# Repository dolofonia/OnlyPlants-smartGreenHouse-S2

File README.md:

# OnlyPlants-smartGreenHouse-S2
 HAN-Project

team:
Mark de Gast, Emiel Visser, Daan Bourgonje, Quintin Meurs, Joris Bol.

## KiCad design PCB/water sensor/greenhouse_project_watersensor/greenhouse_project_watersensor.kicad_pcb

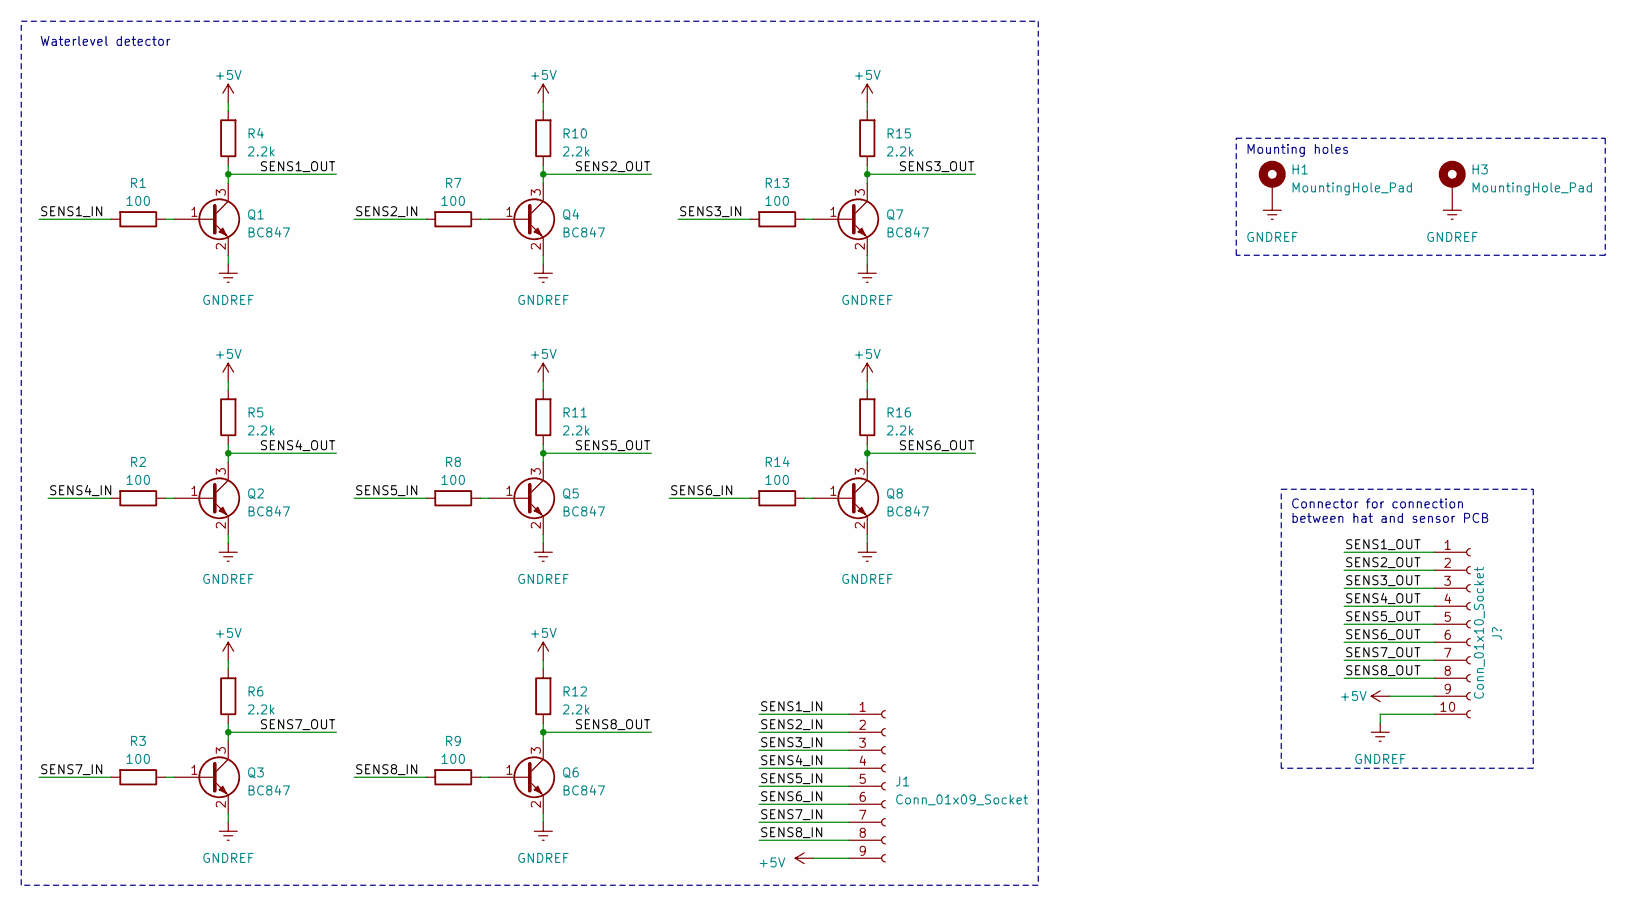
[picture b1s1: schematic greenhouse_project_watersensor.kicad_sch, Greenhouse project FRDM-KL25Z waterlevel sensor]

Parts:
H1, H3: MountingHole_Pad; MountingHole_3.2mm_M3_Pad_Via
J1: Conn_01x09_Socket; PinHeader_1x09_P2.54mm_Vertical
J3: Conn_01x10_Socket; IDC-Header_2x05_P2.54mm_Vertical
Q1, Q2, Q3, Q4, Q5, Q6, Q7, Q8: BC847; SOT-23
R1, R2, R3, R7, R8, R9, R13, R14: 100; R_1206_3216Metric_Pad1.30x1.75mm_HandSolder
R4, R5, R6, R10, R11, R12, R15, R16: 2.2k; R_1206_3216Metric_Pad1.30x1.75mm_HandSolder

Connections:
+5V: J1.9, J3.9, R4.2, R5.2, R6.2, R10.2, R11.2, R12.2, R15.2, R16.2
/SENS1_IN: J1.1, R1.2
/SENS1_OUT: J3.1, Q1.3 (C), R4.1
/SENS2_IN: J1.2, R7.2
/SENS2_OUT: J3.2, Q4.3 (C), R10.1
/SENS3_IN: J1.3, R13.2
/SENS3_OUT: J3.3, Q7.3 (C), R15.1
/SENS4_IN: J1.4, R2.2
/SENS4_OUT: J3.4, Q2.3 (C), R5.1
/SENS5_IN: J1.5, R8.2
/SENS5_OUT: J3.5, Q5.3 (C), R11.1
/SENS6_IN: J1.6, R14.2
/SENS6_OUT: J3.6, Q8.3 (C), R16.1
/SENS7_IN: J1.7, R3.2
/SENS7_OUT: J3.7, Q3.3 (C), R6.1
/SENS8_IN: J1.8, R9.2
/SENS8_OUT: J3.8, Q6.3 (C), R12.1
GNDREF: H1.1, H3.1, J3.10, Q1.2 (E), Q2.2 (E), Q3.2 (E), Q4.2 (E), Q5.2 (E), Q6.2 (E), Q7.2 (E), Q8.2 (E)
unnamed: Q1.1 (B), R1.1
unnamed: Q2.1 (B), R2.1
unnamed: Q3.1 (B), R3.1
unnamed: Q4.1 (B), R7.1
unnamed: Q5.1 (B), R8.1
unnamed: Q6.1 (B), R9.1
unnamed: Q7.1 (B), R13.1
unnamed: Q8.1 (B), R14.1

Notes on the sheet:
Mounting holes
Connector for connection between hat and sensor PCB
Waterlevel detector

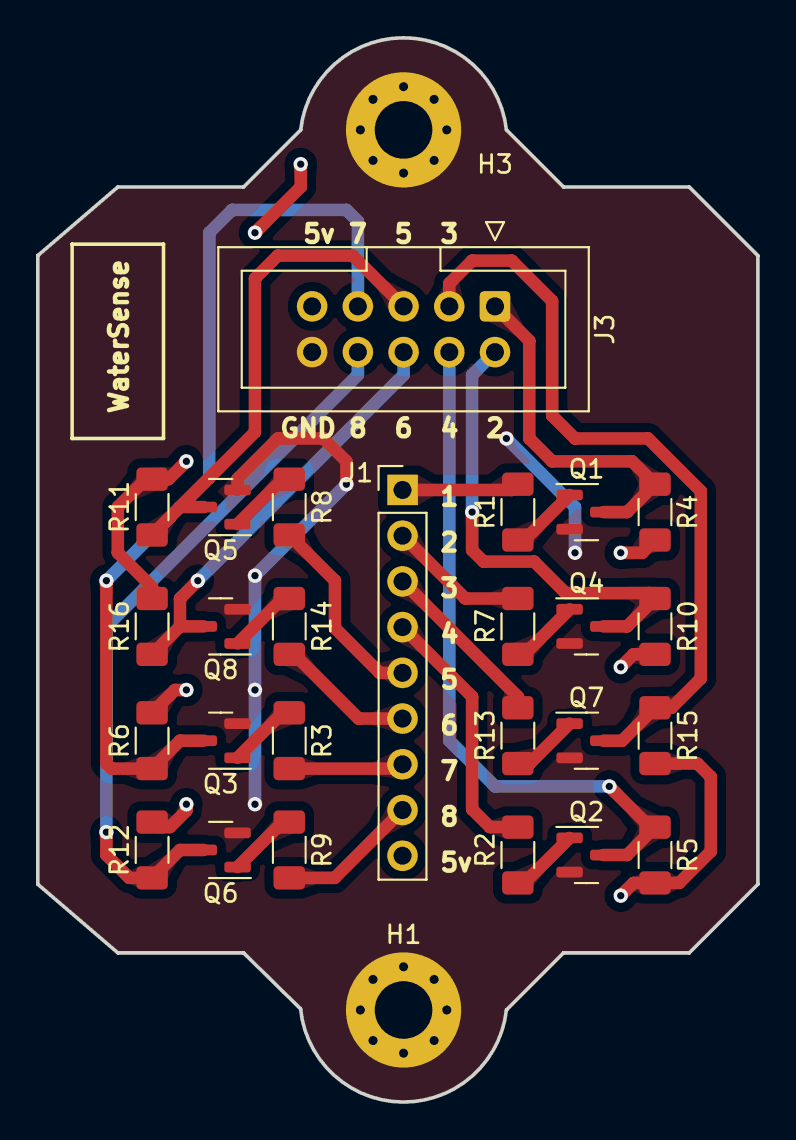
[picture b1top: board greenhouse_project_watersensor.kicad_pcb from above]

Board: 2 copper layers, 40.0 x 59.1 mm, 28 parts (0 on the bottom side), 26 nets.

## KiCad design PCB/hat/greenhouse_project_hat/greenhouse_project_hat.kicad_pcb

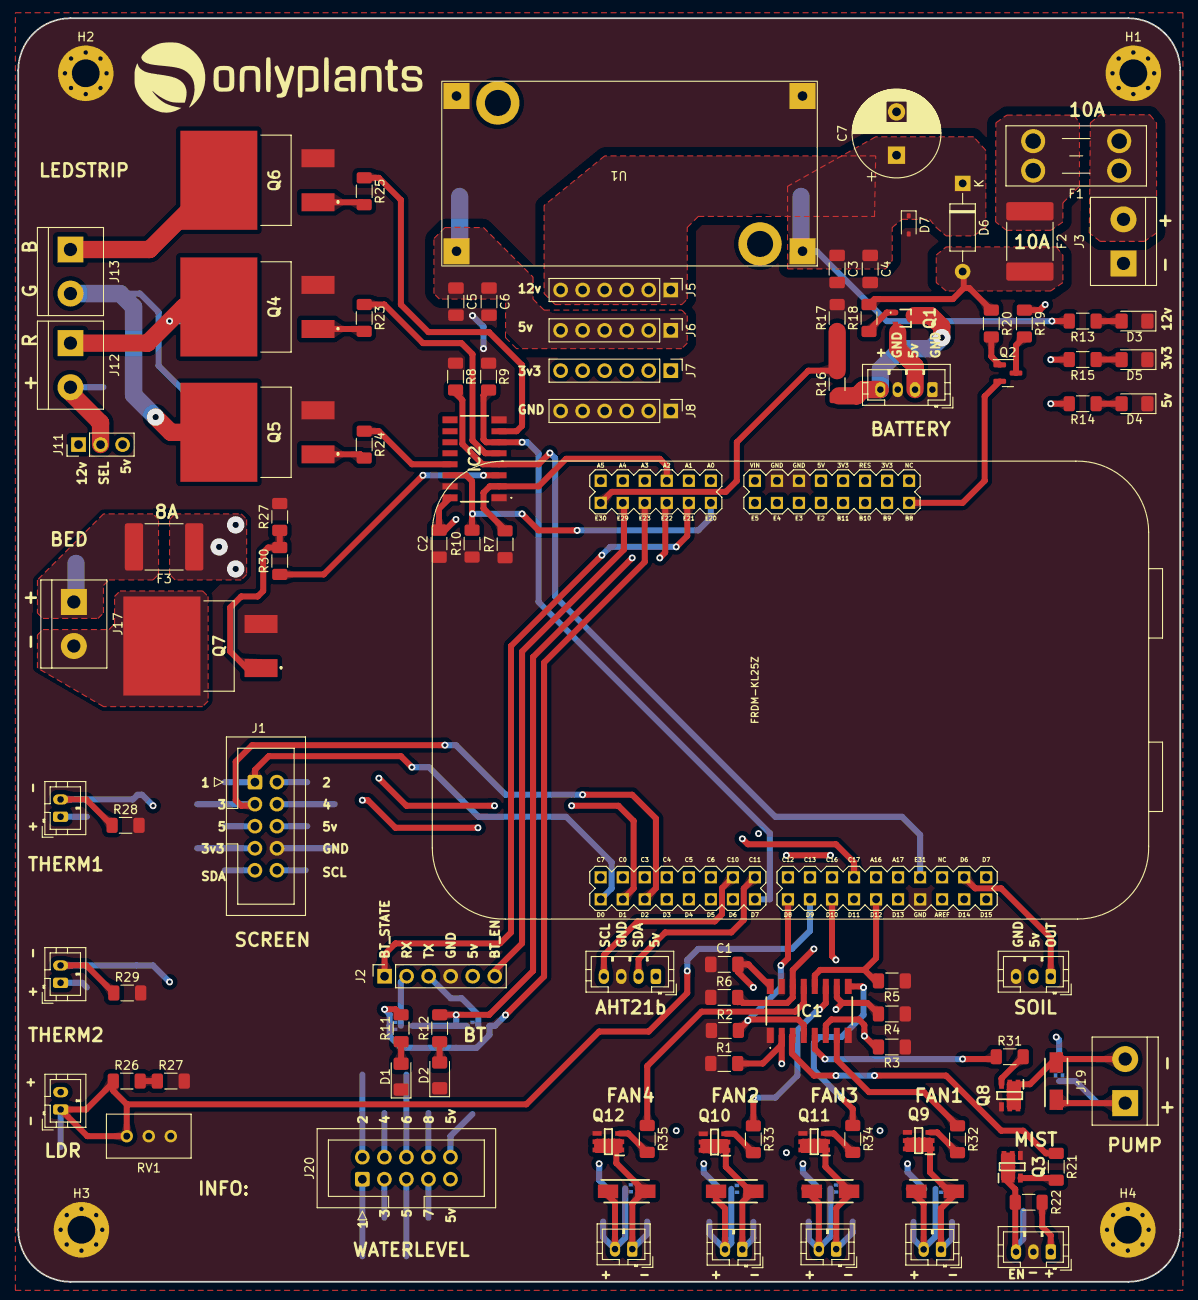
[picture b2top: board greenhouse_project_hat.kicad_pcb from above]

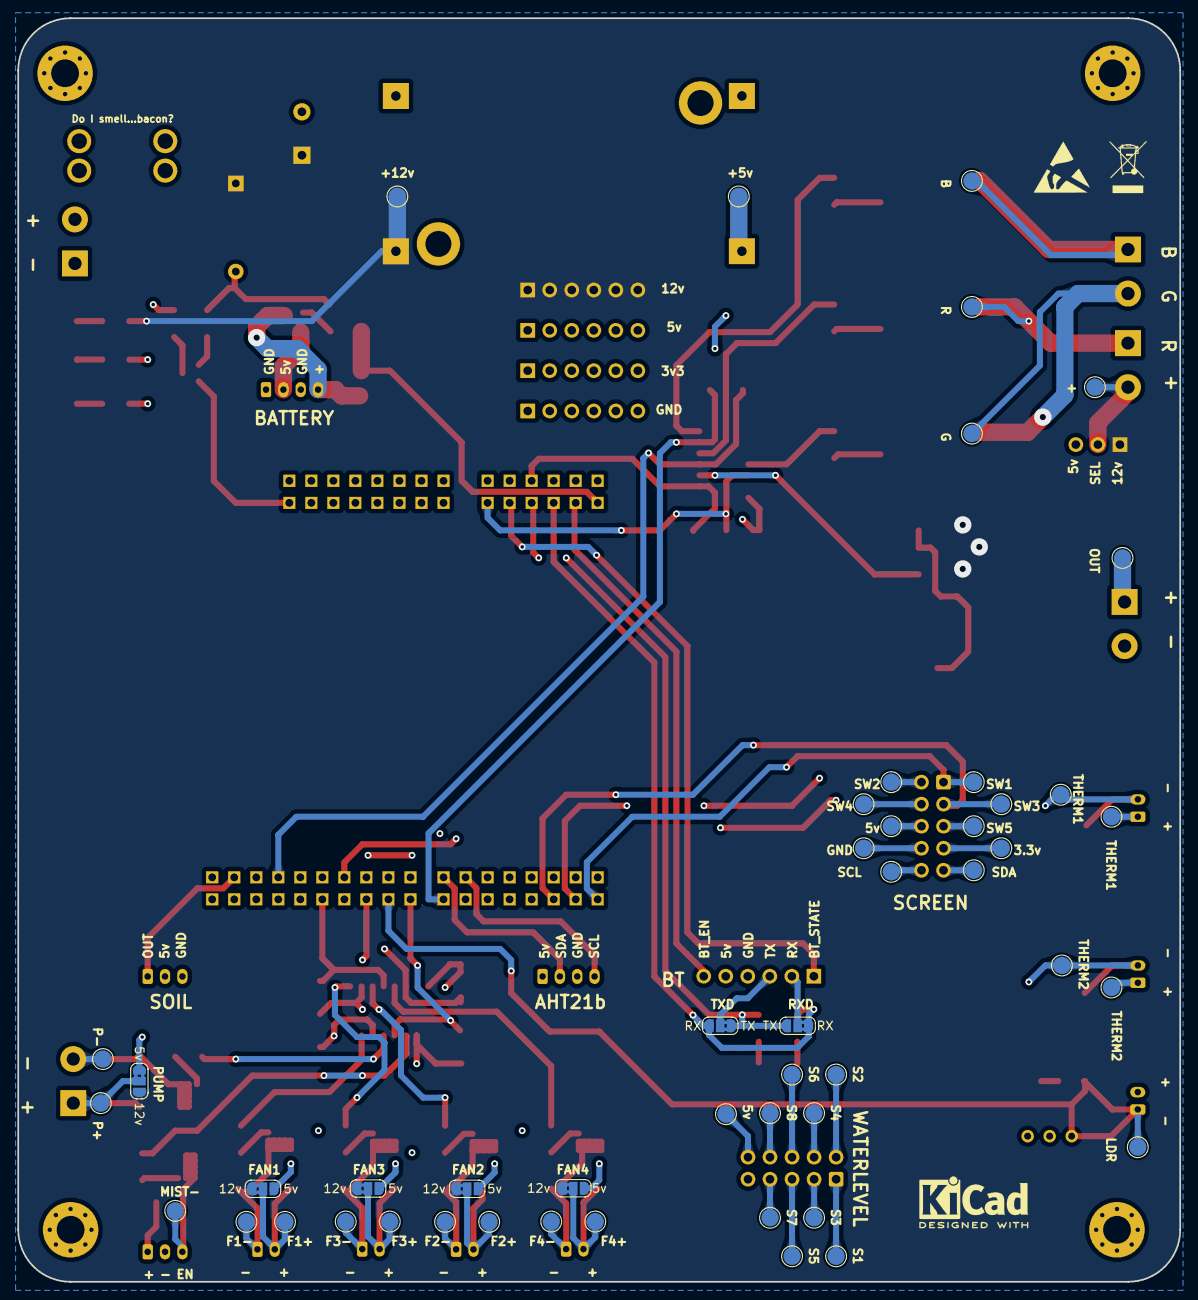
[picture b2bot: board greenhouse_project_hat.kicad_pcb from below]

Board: 4 copper layers, 134.0 x 145.7 mm, 156 parts (52 on the bottom side), 93 nets.

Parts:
C1, C2, C3, C6: 0.1uF; C_1206_3216Metric_Pad1.33x1.80mm_HandSolder
C4, C5: 10uF; C_1206_3216Metric_Pad1.33x1.80mm_HandSolder
C7: 1000uF; CP_Radial_D10.0mm_P5.00mm
D1, D2, D3, D4, D5: LED; LED_1206_3216Metric_Pad1.42x1.75mm_HandSolder
D6: D_Schottky; D_A-405_P10.16mm_Horizontal
D7: BZX384-A13-QX; D_SOD-323
D8, D9, D10, D11, D12: RS2MA-13-F; DIOM5226X230N
F1: Fuse; Fuseholder_Blade_Mini_Keystone_3568
F2, F3: Polyfuse; Fuse_2920_7451Metric_Pad2.10x5.45mm_HandSolder
FRDM1: FRDM-KL25Z; FRDM_KL25Z_NORMAL
G1: LOGO; logo
H1, H2, H3, H4: MountingHole_Pad; MountingHole_3.2mm_M3_Pad_Via
IC1, IC2: 74HCT365D,652; 74HCT365D652
J1, J20: Conn_01x10_Socket; IDC-Header_2x05_P2.54mm_Vertical
J2: Conn_01x06_Socket; PinSocket_1x06_P2.54mm_Vertical
J3, J12, J13, J17, J19: Screw_Terminal_01x02; TerminalBlock_bornier-2_P5.08mm
J4, J10: Conn_01x04_Socket; JST_PH_B4B-PH-K_1x04_P2.00mm_Vertical
J5, J6, J7, J8: Conn_01x06_Pin; PinHeader_1x06_P2.54mm_Vertical
J9, J18: Conn_01x03_Socket; JST_PH_B3B-PH-K_1x03_P2.00mm_Vertical
J11: Conn_01x03_Pin; PinHeader_1x03_P2.54mm_Vertical
J14, J15, J16, J21, J22, J23, J24: Conn_01x02_Socket; JST_PH_B2B-PH-K_1x02_P2.00mm_Vertical
JP1, JP2, JP3, JP4, JP5, JP6, JP7: Jumper_3_Bridged12; SolderJumper-3_P1.3mm_Bridged2Bar12_RoundedPad1.0x1.5mm_Num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
Q1: RZF030P01; 2SB1730
Q2: AO3401A; SOT-23
Q3, Q8, Q9, Q10, Q11, Q12: DMN6040SVT-7; SOT95P280X90-6N
Q4, Q5, Q6, Q7: IRLZ44NSTRLPBF; IRF2804STRLPBF
R1, R2, R3, R4, R5, R6, R7, R8, R9, R10, R13: 10k; R_1206_3216Metric_Pad1.30x1.75mm_HandSolder
R11, R12: 5k; R_1206_3216Metric_Pad1.30x1.75mm_HandSolder
R14, R22: 4.7k; R_1206_3216Metric_Pad1.30x1.75mm_HandSolder
R15: 2.2k; R_1206_3216Metric_Pad1.30x1.75mm_HandSolder
R16: 49.9K; R_1206_3216Metric_Pad1.30x1.75mm_HandSolder
R17: 10K; R_1206_3216Metric_Pad1.30x1.75mm_HandSolder
R18, R19, R20: 165; R_1206_3216Metric_Pad1.30x1.75mm_HandSolder
R21, R23, R24, R25, R30, R31, R32, R33, R34, R35: 1k; R_1206_3216Metric_Pad1.30x1.75mm_HandSolder
R26, R28, R29: 100k; R_1206_3216Metric_Pad1.30x1.75mm_HandSolder
R27: 12k; R_1206_3216Metric_Pad1.30x1.75mm_HandSolder
R27#2: 0; R_1206_3216Metric_Pad1.30x1.75mm_HandSolder
REF1: KiCad-Logo2_5mm_SilkScreen
REF2: WEEE-Logo_4.2x6mm_SilkScreen
REF3: ESD-Logo_6.6x6mm_SilkScreen
RV1: R_Potentiometer; Potentiometer_Bourns_3296W_Vertical
TP1, TP2, TP3, TP4, TP5, TP6, TP7, TP8, TP9, TP10, TP11, TP12, TP13, TP14, TP15, TP16, TP17, TP18, TP19, TP20, TP21, TP22, TP23, TP24, TP25, TP26, TP27, TP28, TP29, TP30, TP31, TP32, TP33, TP34, TP35, TP36, TP37, TP38, TP39, TP40, TP41, TP42: TestPoint; TestPoint_Pad_D2.0mm
U1: LM2596 Buck; LM2596_Buck_module

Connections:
+3.3V: FRDM1.P3V3 (3V3), J1.7, J7.1, J7.2, J7.3, J7.4, J7.5, J7.6, J14.2, J15.1, J16.1, R15.2, R19.1, TP7.1, TP19.1, TP20.1
+5V: C1.2, C2.2, C5.1, C6.1, FRDM1.VIN, IC1.16 (VCC), IC2.16 (VCC), J1.6, J2.5, J4.2, J6.1, J6.2, J6.3, J6.4, J6.5, J6.6, J9.1, J10.1, J11.3, J18.2, J20.9, J20.10, JP3.1 (A), JP4.3 (B), JP5.3 (B), JP6.3 (B), JP7.3 (B), Q1.2, R14.2, R22.2, TP6.1, TP11.1, TP34.1, U1.3 (OUT+)
+12V: C3.1, C4.1, C7.1, D6.1 (K), D7.1 (K), F3.1, J5.1, J5.2, J5.3, J5.4, J5.5, J5.6, J11.1, JP3.3 (B), JP4.1 (A), JP5.1 (A), JP6.1 (A), JP7.1 (A), R13.2, TP12.1, U1.1 (IN+)
/BT_EN: FRDM1.PTE29, J2.6
/BT_RXD: FRDM1.PTE23, JP1.1 (A), JP2.3 (B), R11.2
/BT_RXD_O: J2.2, JP1.2 (C)
/BT_STATE: FRDM1.PTE21, J2.1
/BT_TXD: FRDM1.PTE22, JP1.3 (B), JP2.1 (A), R12.2
/BT_TXD_O: J2.3, JP2.2 (C)
/Fans/Fan1+: D9.1, J21.2, JP4.2 (C), TP37.1
/Fans/Fan1-: D9.2, J21.1, Q9.1 (D_1), Q9.2 (D_2), Q9.5 (D_3), Q9.6 (D_4), TP35.1
/Fans/Fan2+: D10.1, J22.2, JP5.2 (C), TP38.1
/Fans/Fan2-: D10.2, J22.1, Q10.1 (D_1), Q10.2 (D_2), Q10.5 (D_3), Q10.6 (D_4), TP36.1
/Fans/Fan3+: D11.1, J23.2, JP6.2 (C), TP41.1
/Fans/Fan3-: D11.2, J23.1, Q11.1 (D_1), Q11.2 (D_2), Q11.5 (D_3), Q11.6 (D_4), TP39.1
/Fans/Fan4+: D12.1, J24.2, JP7.2 (C), TP42.1
/Fans/Fan4-: D12.2, J24.1, Q12.1 (D_1), Q12.2 (D_2), Q12.5 (D_3), Q12.6 (D_4), TP40.1
/Heating/BED_OUT: F3.2, J17.1, TP23.1
/Humidifier/MIST-: J9.3, Q3.1 (D_1), Q3.2 (D_2), Q3.5 (D_3), Q3.6 (D_4), R22.1, TP13.1
/OLED_SCL: FRDM1.D15 (SCL/PTE1), J1.10, TP10.1
/OLED_SDA: FRDM1.D14 (SDA/PTE0), J1.9, TP9.1
/Power/BATT_EN: D6.2 (A), F2.2, R18.2, R20.1
/Power/BATT_IN: J4.4, Q1.3, R16.1
/SW1_OUT: FRDM1.D0 (D0/PTA1), J1.1, TP1.1
/SW2_OUT: FRDM1.D1 (D1/PTA2), J1.2, TP2.1
/SW3_OUT: FRDM1.D2 (D2/PTD4), J1.3, TP3.1
/SW4_OUT: FRDM1.D3 (D3/PTA12), J1.4, TP4.1
/SW5_OUT: FRDM1.D4 (D4/PTA4), J1.5, TP5.1
/Water/Pump+: D8.1, J19.1, JP3.2 (C), TP25.1
/Water/Pump-: D8.2, J19.2, Q8.1 (D_1), Q8.2 (D_2), Q8.5 (D_3), Q8.6 (D_4), TP24.1
AHT_SCL: FRDM1.PTC10, J10.4
AHT_SDA: FRDM1.PTC11, J10.2
BATT_V: FRDM1.PTE30, R16.2, R17.1
B_IN: FRDM1.D7 (D7/PTC9), IC2.6 (3A), R9.2
B_IN_POW: IC2.7 (3Y), R25.1
FAN1_IN: FRDM1.D10 (D10/PTD0), IC1.6 (3A), R3.2
FAN1_IN_POW: IC1.7 (3Y), R32.1
FAN2_IN: FRDM1.D11 (D11/PTD2), IC1.10 (4A), R4.2
FAN2_IN_POW: IC1.9 (4Y), R34.1
FAN3_IN: FRDM1.D12 (D12/PTD3), IC1.12 (5A), R5.2
FAN3_IN_POW: IC1.11 (5Y), R33.1
FAN4_IN: FRDM1.D13 (D13/PTD1), IC1.14 (6A), R6.2
FAN4_IN_POW: IC1.13 (6Y), R35.1
GNDREF: C1.1, C2.1, C3.2, C4.2, C5.2, C6.2, C7.2, D1.1 (K), D2.1 (K), D3.1 (K), D4.1 (K), D5.1 (K), D7.2 (A), FRDM1.GND0, FRDM1.GND1, FRDM1.GND2, H1.1, H2.1, H3.1, H4.1, IC1.1 (~OE1), IC1.8 (GND), IC1.15 (~OE2), IC2.1 (~OE1), IC2.8 (GND), IC2.15 (~OE2), J1.8, J2.4, J3.1, J4.1, J4.3, J8.1, J8.2, J8.3, J8.4, J8.5, J8.6, J9.2, J10.3, J18.3, Q3.4 (S), Q4.3, Q5.3, Q6.3, Q7.3, Q8.4 (S), Q9.4 (S), Q10.4 (S), Q11.4 (S), Q12.4 (S), R1.1, R2.1, R3.1, R4.1, R5.1, R6.1, R7.1, R8.1, R9.1, R10.1, R17.2, R27.2, R27#2.2, R28.2, R29.2, RV1.2, RV1.3, TP8.1, U1.2 (IN-), U1.4 (OUT-)
G_IN: FRDM1.PTE20, IC2.14 (6A), R10.2
G_IN_POW: IC2.13 (6Y), R24.1
HEATER_IN: FRDM1.A2 (A2/PTB2), IC2.2 (1A), R7.2
HEATER_IN_POW: IC2.3 (1Y), R30.1
HUM_OUT: FRDM1.PTD6, J18.1
LDR_OUT: FRDM1.D9 (D9/PTD5), J14.1, R26.1, RV1.1, TP18.1
MIST_EN: FRDM1.PTC6, IC1.2 (1A), R1.2
MIST_EN_POW: IC1.3 (1Y), R21.1
unnamed: D1.2 (A), R11.1
unnamed: D2.2 (A), R12.1
unnamed: D3.2 (A), R13.1
unnamed: D4.2 (A), R14.1
unnamed: D5.2 (A), R15.1
unnamed: F1.2, F2.1
unnamed: J11.2, J12.2, TP17.1
unnamed: J12.1, Q4.2, TP14.1
unnamed: J13.1, Q6.2, TP16.1
unnamed: J13.2, Q5.2, TP15.1
unnamed: J17.2, Q7.2
unnamed: Q1.1, R18.1
unnamed: Q2.3 (D), R19.2
unnamed: Q2.1 (G), R20.2
unnamed: Q3.3 (G), R21.2
unnamed: Q4.1, R23.2
unnamed: Q5.1, R24.2
unnamed: Q6.1, R25.2
unnamed: Q7.1, R27.1, R30.2
unnamed: Q8.3 (G), R31.2
unnamed: Q9.3 (G), R32.2
unnamed: Q10.3 (G), R33.2
unnamed: Q11.3 (G), R34.2
unnamed: Q12.3 (G), R35.2
unnamed: R26.2, R27#2.1
PUMP_IN: FRDM1.D8 (D8/PTA13), IC1.4 (2A), R2.2
PUMP_IN_POW: IC1.5 (2Y), R31.1
R_IN: FRDM1.PTE31, IC2.4 (2A), R8.2
R_IN_POW: IC2.5 (2Y), R23.1
SENS1: FRDM1.PTC12, J20.1, TP26.1
SENS2: FRDM1.PTC13, J20.2, TP27.1
SENS3: FRDM1.PTC16, J20.3, TP28.1
SENS4: FRDM1.PTC17, J20.4, TP29.1
SENS5: FRDM1.PTA16, J20.5, TP30.1
SENS6: FRDM1.PTA17, J20.6, TP31.1
SENS7: FRDM1.D5 (D5/PTA5), J20.7, TP32.1
SENS8: FRDM1.PTD7, J20.8, TP33.1
THERM1: FRDM1.A0 (A0/PTB0), J15.2, R28.1, TP22.1
THERM2: FRDM1.A1 (A1/PTB1), J16.2, R29.1, TP21.1
VDC: F1.1, J3.2
~12V_EN: FRDM1.PTB8, Q2.2 (S)

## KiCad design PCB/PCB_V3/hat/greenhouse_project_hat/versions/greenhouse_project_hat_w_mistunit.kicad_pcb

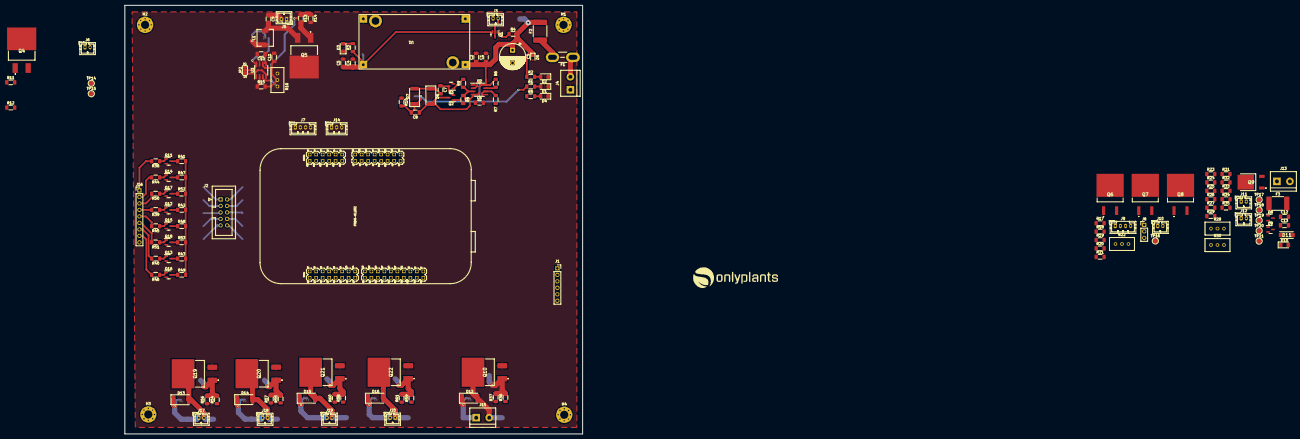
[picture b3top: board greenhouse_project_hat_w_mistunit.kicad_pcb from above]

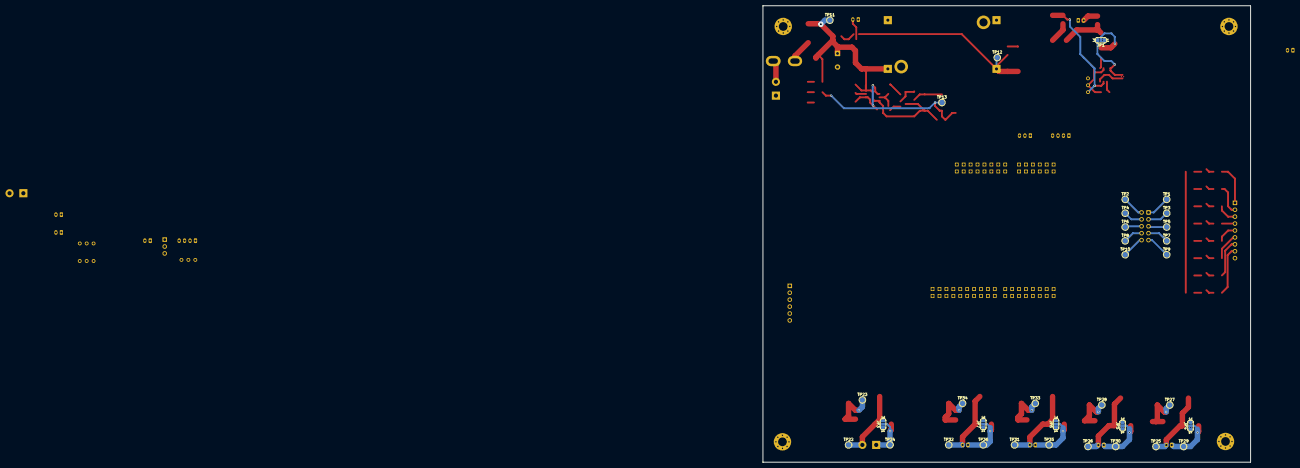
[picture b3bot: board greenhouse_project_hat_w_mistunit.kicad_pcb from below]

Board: 2 copper layers, 179.1 x 167.6 mm, 187 parts (34 on the bottom side), 90 nets.

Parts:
C1, C5, C12, C13: 0.1uF; C_1206_3216Metric_Pad1.33x1.80mm_HandSolder
C2, C4: 10uF; C_1206_3216Metric_Pad1.33x1.80mm_HandSolder
C3: 1000uF; CP_Radial_D10.0mm_P5.00mm
C6: 470nF; C_1206_3216Metric_Pad1.33x1.80mm_HandSolder
C7: 330uF; C_1206_3216Metric_Pad1.33x1.80mm_HandSolder
C8: 3.3nF; C_1206_3216Metric_Pad1.33x1.80mm_HandSolder
C9, C10: 100nF; C_1206_3216Metric_Pad1.33x1.80mm_HandSolder
C11: 10nF; C_1206_3216Metric_Pad1.33x1.80mm_HandSolder
D1, D2, D3, D4, D10: LED; LED_1206_3216Metric_Pad1.42x1.75mm_HandSolder
D5: BZX384-A13-QX; D_SOD-323
D6, D7, D12, D13, D14, D15, D16: 1N4007; D_2512_6332Metric_Pad1.52x3.35mm_HandSolder
D8, D9: BAV99; SOT-23
D11: SS54; DIOM5126X245N
F1: Fuse; Fuse_Blade_Mini_directSolder
F2, F3: Polyfuse; Fuse_2920_7451Metric_Pad2.10x5.45mm_HandSolder
FRDM1: FRDM-KL25Z; FRDM_KL25Z_NORMAL
H1, H2, H3, H4: MountingHole_Pad; MountingHole_3.2mm_M3_Pad_Via
J1: Conn_01x06_Socket; PinSocket_1x06_P2.54mm_Vertical
J2: Conn_01x10_Socket; IDC-Header_2x05_P2.54mm_Vertical
J3, J5, J6, J10, J11, J12, J17, J18, J19, J20: Conn_01x02_Socket; JST_PH_B2B-PH-K_1x02_P2.00mm_Vertical
J4, J13, J15: Screw_Terminal_01x02; TerminalBlock_bornier-2_P5.08mm
J7, J9: Conn_01x04_Socket; JST_PH_B4B-PH-K_1x04_P2.00mm_Vertical
J8: Conn_01x03_Pin; PinHeader_1x03_P2.54mm_Vertical
J14: Conn_01x03_Socket; JST_PH_B3B-PH-K_1x03_P2.00mm_Vertical
J16: Conn_01x09_Socket; PinHeader_1x09_P2.54mm_Vertical
JP1, JP2, JP3, JP4, JP5, JP6, JP7: Jumper_3_Bridged12; SolderJumper-3_P1.3mm_Bridged2Bar12_RoundedPad1.0x1.5mm_Num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
L1: 220uH; L_6.3x6.3_H3
Q1: AO3401A; SOT-23
Q2, Q3, Q11, Q12, Q13, Q14, Q15, Q16, Q17, Q18: BC847; SOT-23
Q4, Q5, Q10, Q19, Q20, Q21, Q22: IRLZ44NSTRLPBF; IRF2804STRLPBF
Q6, Q7, Q8: IRF640S
Q9: IPD036N04LGATMA1
R1: 750; R_1206_3216Metric_Pad1.30x1.75mm_HandSolder
R2, R12, R17, R18, R19, R33, R37, R56, R57, R60, R61: 10k; R_1206_3216Metric_Pad1.30x1.75mm_HandSolder
R3, R23, R24, R35: 4.7k; R_1206_3216Metric_Pad1.30x1.75mm_HandSolder
R4: 165; R_1206_3216Metric_Pad1.30x1.75mm_HandSolder
R5, R11, R36, R41, R42, R43, R47, R48, R49, R52, R53, R54, R55, R58, R59: 2.2k; R_1206_3216Metric_Pad1.30x1.75mm_HandSolder
R6: 1k; R_1206_3216Metric_Pad1.30x1.75mm_HandSolder
R7: 3.3k; R_1206_3216Metric_Pad1.30x1.75mm_HandSolder
R8, R9: 820; R_1206_3216Metric_Pad1.30x1.75mm_HandSolder
R10: 25; R_1206_3216Metric_Pad1.30x1.75mm_HandSolder
R13, R15: 10; R_1206_3216Metric_Pad1.30x1.75mm_HandSolder
R14, R21, R31, R32: 0; R_1206_3216Metric_Pad1.30x1.75mm_HandSolder
R16, R22, R28, R30: R_Variable; Potentiometer_Bourns_3296W_Vertical
R20: 100k; R_1206_3216Metric_Pad1.30x1.75mm_HandSolder
R25, R26, R27, R29: 2.37k 1%; R_1206_3216Metric_Pad1.30x1.75mm_HandSolder
R34: 12k; R_1206_3216Metric_Pad1.30x1.75mm_HandSolder
R38, R39, R40, R44, R45, R46, R50, R51: 100; R_1206_3216Metric_Pad1.30x1.75mm_HandSolder
TP1, TP2, TP3, TP4, TP5, TP6, TP7, TP8, TP9, TP10, TP11, TP12, TP13, TP14, TP15, TP16, TP17, TP18, TP19, TP20, TP21, TP22, TP23, TP24, TP25, TP26, TP27, TP28, TP29, TP30, TP31, TP32, TP33, TP34, TP35, TP36: TestPoint; TestPoint_Pad_D2.0mm
U1: LM2596 Buck; LM2596_Buck_module
U2, U3: NE555D; SOIC-8_3.9x4.9mm_P1.27mm

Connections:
+3.3V: D8.1 (K), D9.1 (K), J2.7, R5.1, R23.1, R24.1, TP7.1
+12V: C1.1, C2.1, C3.1, C8.1, D5.1 (K), D6.2 (A), F2.2, F3.1, J8.1, JP1.1 (A), JP3.3 (B), JP4.1 (A), JP5.1 (A), JP6.1 (A), JP7.1 (A), Q2.3 (C), R2.1, R4.2, R6.1, TP11.1, U1.1 (IN+), U2.4 (R), U2.8 (VCC)
+15V: C8.2, D7.1 (K), JP1.3 (B), JP2.2 (C), R1.1, R10.2, TP13.1, U3.8 (VCC)
/Fans/Fan1+: D13.1 (K), J17.1, JP4.2 (C), TP29.1
/Fans/Fan1-: D13.2 (A), J17.2, Q19.2, TP25.1
/Fans/Fan2+: D14.1 (K), J18.1, JP5.2 (C), TP30.1
/Fans/Fan2-: D14.2 (A), J18.2, Q20.2, TP26.1
/Fans/Fan3+: D15.1 (K), J19.1, JP6.2 (C), TP35.1
/Fans/Fan3-: D15.2 (A), J19.2, Q21.2, TP31.1
/Fans/Fan4+: D16.1 (K), J20.1, JP7.2 (C), TP36.1
/Fans/Fan4-: D16.2 (A), J20.2, Q22.2, TP32.1
/Heating/BED_OUT: D10.1 (K), D11.2, J13.1, Q9.2, TP21.1
/Humidifier/MIST-: J6.2, Q4.2, TP15.1
/Humidifier/piezo+: C9.1, J5.2
/OLED_SCL: J2.10, TP10.1
/OLED_SDA: J2.9, TP9.1
/OUT_SW1: J2.1, TP1.1
/OUT_SW2: J2.2, TP2.1
/OUT_SW3: J2.3, TP3.1
/OUT_SW4: J2.4, TP4.1
/OUT_SW5: J2.5, TP5.1
/Power/BATT_IN: J3.2, Q1.3 (D)
/Water/Pump+: D12.1 (K), J15.1, JP3.2 (C), TP24.1
/Water/Pump-: D12.2 (A), J15.2, Q10.2, TP22.1
ANODE: C4.1, C5.1, J1.5, J2.6, J6.1, J7.1, J8.3, J10.2, J14.2, J16.9, JP3.1 (A), JP4.3 (B), JP5.3 (B), JP6.3 (B), JP7.3 (B), Q1.2 (S), R3.1, R41.2, R42.2, R43.2, R47.2, R48.2, R49.2, R52.2, R53.2, TP6.1, TP12.1, U1.3 (OUT+)
B_IN: Q8.1, R19.1
GNDREF: C1.2, C2.2, C3.2, C4.2, C5.2, C6.2, C10.2, C11.2, C12.2, C13.2, D1.1 (K), D2.1 (K), D3.1 (K), D4.1 (K), D5.2 (A), D8.2 (A), D9.2 (A), H1.1, H2.1, H3.1, H4.1, J1.4, J2.8, J3.1, J4.1, J5.1, J7.3, J11.2, J12.2, J13.2, J14.3, Q3.2 (E), Q4.3, Q5.2, Q6.3, Q7.3, Q8.3, Q9.3, Q10.3, Q11.2 (E), Q12.2 (E), Q13.2 (E), Q14.2 (E), Q15.2 (E), Q16.2 (E), Q17.2 (E), Q18.2 (E), Q19.3, Q20.3, Q21.3, Q22.3, R10.1, R12.1, R17.2, R18.2, R19.2, R21.1, R22.2, R34.2, R37.1, R56.1, R57.1, R60.1, R61.1, TP8.1, U1.2 (IN-), U1.4 (OUT-), U1.5 (GND1), U1.6 (GND2), U2.1 (GND), U3.1 (GND)
G_IN: Q7.1, R18.1
LDR_OUT: J10.1, R20.1, R22.1, TP16.1
MIST_EN: R11.1, R15.1, U3.2 (TR)
unnamed: C9.2, L1.2, Q5.3
unnamed: D1.2 (A), R1.2
unnamed: D2.2 (A), R2.2
unnamed: D3.2 (A), R3.2
unnamed: D4.2 (A), R5.2
unnamed: C7.2, D6.1 (K), D7.2 (A)
unnamed: D8.3 (K), R25.2, R27.1, R28.1
unnamed: D9.3 (K), R26.2, R29.1, R30.1
unnamed: D10.2 (A), R35.1
unnamed: D11.1, F3.2, R35.2
unnamed: F1.2, F2.1
unnamed: J8.2, J9.1
unnamed: J9.2, Q6.2
unnamed: J9.3, Q7.2
unnamed: J9.4, Q8.2
unnamed: J11.1, R23.2, R25.1, TP17.1
unnamed: J12.1, R24.2, R26.1, TP18.1
unnamed: JP1.2 (C), L1.1
unnamed: JP2.1 (A), U3.4 (R)
unnamed: Q1.1 (G), R4.1
unnamed: Q2.1 (B), R8.2
unnamed: C7.1, Q2.2 (E), Q3.3 (C)
unnamed: Q3.1 (B), R9.2
unnamed: Q4.1, R11.2, R12.2, TP14.1
unnamed: Q5.1, R13.2
unnamed: Q9.1, R33.1, R34.1
unnamed: Q10.1, R36.2, R37.2, TP23.1
unnamed: Q11.1 (B), R38.1
unnamed: Q12.1 (B), R39.1
unnamed: Q13.1 (B), R40.1
unnamed: Q14.1 (B), R44.1
unnamed: Q15.1 (B), R45.1
unnamed: Q16.1 (B), R46.1
unnamed: Q17.1 (B), R50.1
unnamed: Q18.1 (B), R51.1
unnamed: Q19.1, R54.2, R56.2, TP27.1
unnamed: Q20.1, R55.2, R57.2, TP28.1
unnamed: Q21.1, R58.2, R60.2, TP33.1
unnamed: Q22.1, R59.2, R61.2, TP34.1
unnamed: R20.2, R21.2
unnamed: R27.2, R31.1
unnamed: R29.2, R32.1
unnamed: R6.2, R7.1, U2.7 (DIS)
unnamed: R8.1, R9.1, U2.3 (Q)
unnamed: C6.1, R7.2, U2.2 (TR), U2.6 (THR)
unnamed: C10.1, U3.5 (CV)
unnamed: C11.1, R15.2, R16.2, U3.6 (THR)
R_IN: Q6.1, R17.1
SENS1: J16.1, Q11.3 (C), R38.2, R41.1
SENS2: J16.2, Q14.3 (C), R44.2, R47.1
SENS3: J16.3, Q17.3 (C), R50.2, R52.1
SENS4: J16.4, Q12.3 (C), R39.2, R42.1
SENS5: J16.5, Q15.3 (C), R45.2, R48.1
SENS6: J16.6, Q18.3 (C), R51.2, R53.1
SENS7: J16.7, Q13.3 (C), R40.2, R43.1
SENS8: J16.8, Q16.3 (C), R46.2, R49.1
THERM0: C12.1, R28.2, R31.2, TP19.1
THERM1: C13.1, R30.2, R32.2, TP20.1
VDC: F1.1, J4.2
adj: R13.1, R14.1, R16.1, U3.3 (Q)

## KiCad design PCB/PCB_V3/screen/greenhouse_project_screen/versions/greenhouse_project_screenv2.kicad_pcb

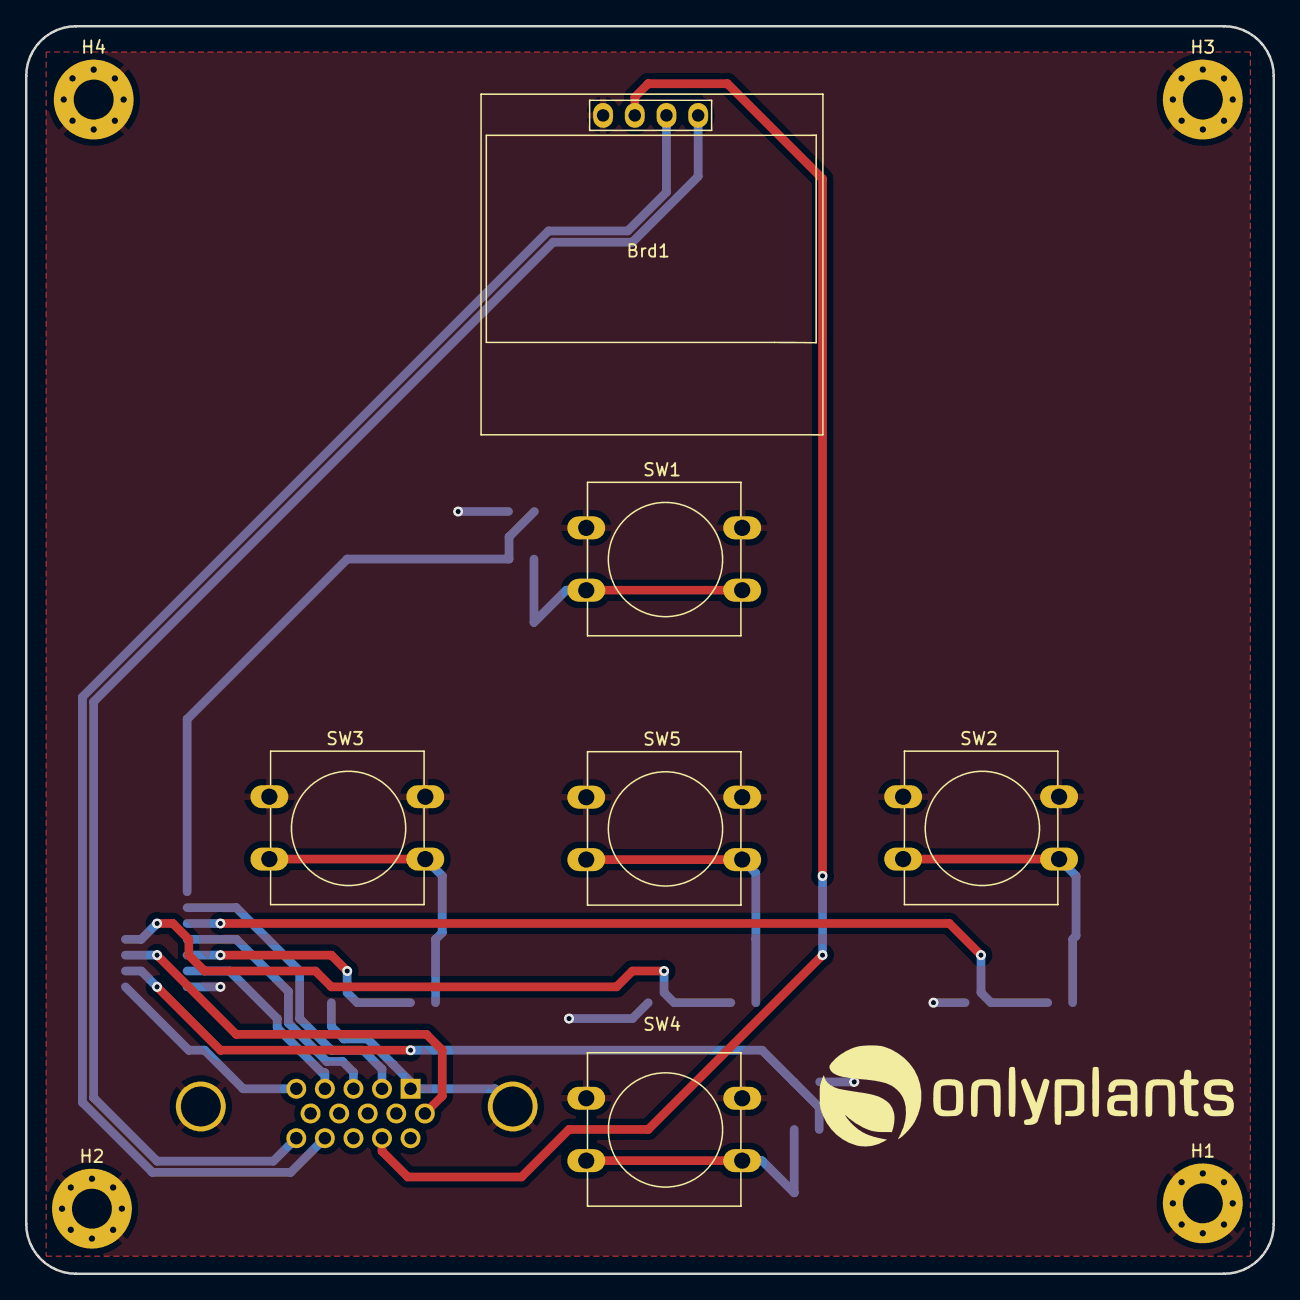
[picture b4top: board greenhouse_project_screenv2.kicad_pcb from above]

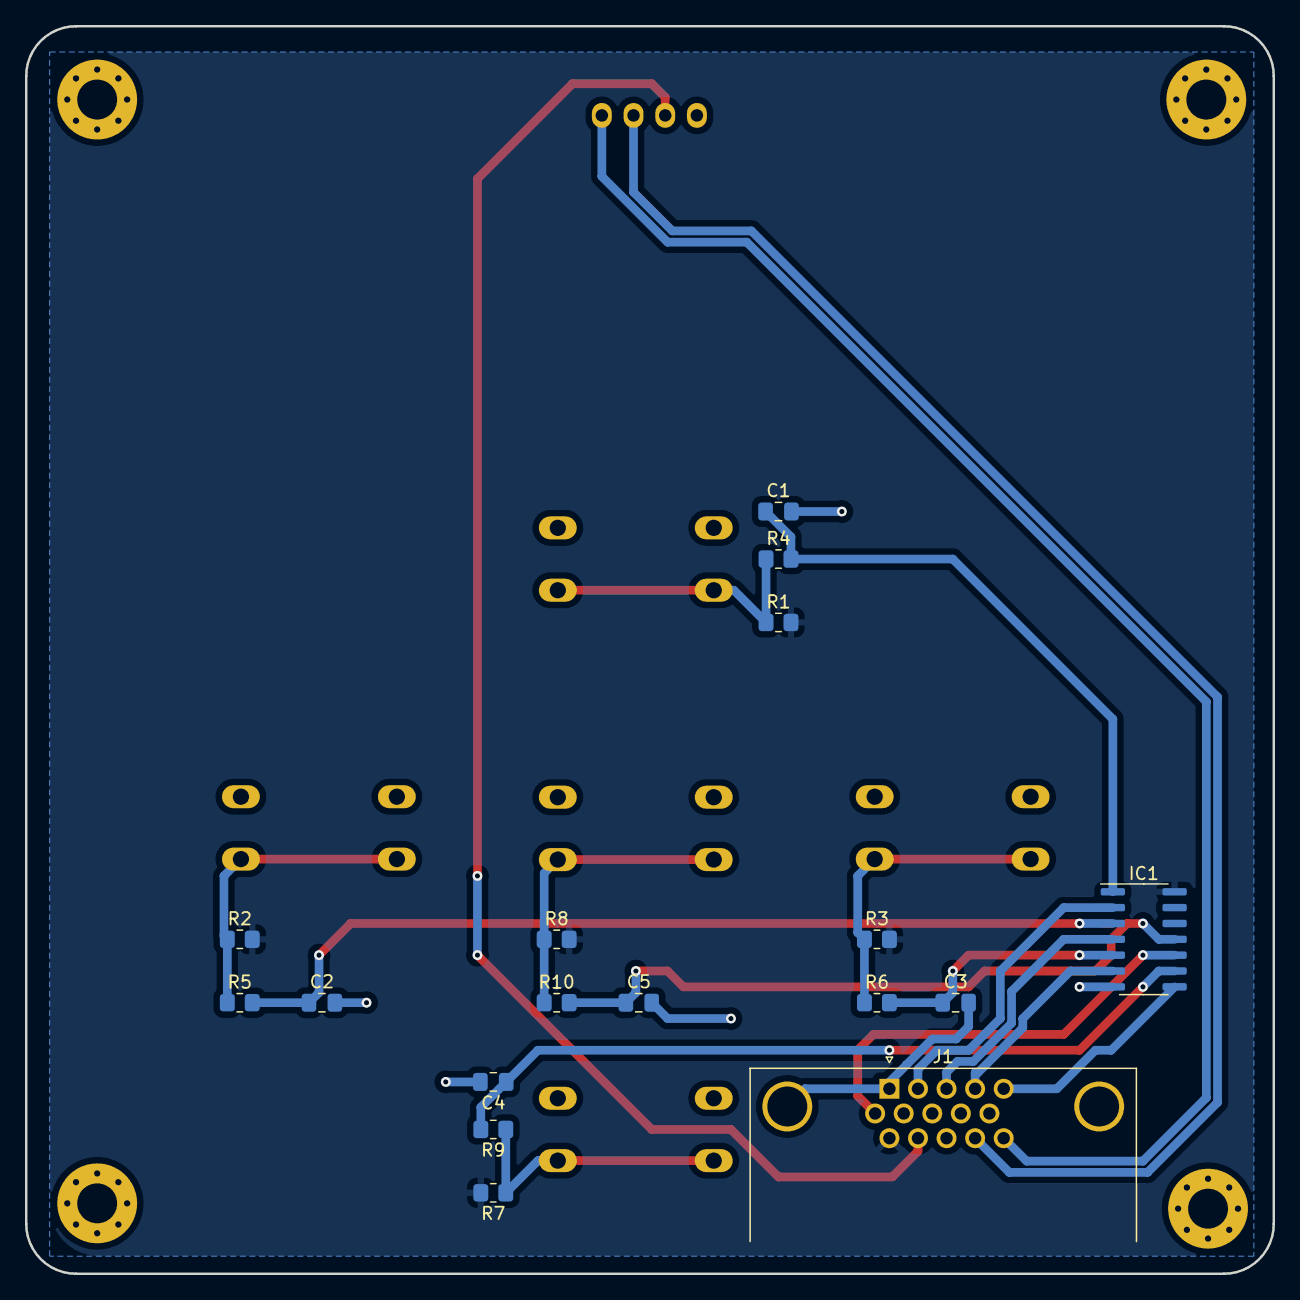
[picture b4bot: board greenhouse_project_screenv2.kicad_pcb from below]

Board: 2 copper layers, 100.0 x 100.0 mm, 27 parts (17 on the bottom side), 20 nets.

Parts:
Brd1: SSD1306; 128x64OLED
C1, C2, C3, C4, C5: C; C_0805_2012Metric_Pad1.18x1.45mm_HandSolder
H1, H2, H3, H4: MountingHole_Pad; MountingHole_3.2mm_M3_Pad_Via
IC1: CD74HC14M96; SOIC-14_3.9x8.7mm_P1.27mm
J1: DE15_Receptacle_HighDensity_MountingHoles; DSUB-15-HD_Male_Horizontal_P2.29x1.98mm_EdgePinOffset8.35mm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
R1, R2, R3, R4, R5, R6, R7, R8, R9, R10: R; R_0805_2012Metric_Pad1.20x1.40mm_HandSolder
SW1, SW2, SW3, SW4, SW5: SW_Push; SW_PUSH-12mm

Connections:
+3.3V: IC1.14 (VCC), J1.11, R1.2, R2.2, R3.2, R7.2, R8.2
+5V: Brd1.2 (VCC), J1.12
/IN_SW1: C1.1, IC1.1 (1A), R4.2
/IN_SW2: C2.1, IC1.3 (2A), R5.2
/IN_SW3: C3.1, IC1.5 (3A), R6.2
/IN_SW4: C4.1, IC1.9 (4A), R9.2
/IN_SW5: C5.1, IC1.11 (5A), R10.2
/OUT_SW1: IC1.2 (1Y), J1.2
/OUT_SW2: IC1.4 (2Y), J1.3
/OUT_SW3: IC1.6 (3Y), J1.4
/OUT_SW4: IC1.8 (4Y), J1.5
/OUT_SW5: IC1.10 (5Y), J1.6
/SCL: Brd1.3 (SCL), J1.14
/SDA: Brd1.4 (SDA), J1.15
GNDREF: Brd1.1 (GND), C1.2, C2.2, C3.2, C4.2, C5.2, H1.1, H2.1, H3.1, H4.1, IC1.7 (GND), J1.0, J1.1, SW1.1, SW2.1, SW3.1, SW4.1, SW5.1
unnamed: R1.1, R4.1, SW1.2
unnamed: R2.1, R5.1, SW2.2
unnamed: R3.1, R6.1, SW3.2
unnamed: R7.1, R9.1, SW4.2
unnamed: R8.1, R10.1, SW5.2
